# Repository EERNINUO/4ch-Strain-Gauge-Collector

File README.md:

<div align="center">

<!-- Assisted-by: DeepSeek - 文档框架 -->

# 4ch-Strain-Gauge-Collector

创新创业实践课程设计 E4 选题 – 4通道应变信号同步采集模块  
基于 STM32G473，内置 ADC + 高速 SRAM 缓冲 + USB 触发同步

<p align="center">

  <br/>

</p>

</div>

---

## 📌 项目简介

本项目为《创新创业实践课程》课程 E4 选题的硬件与固件设计成果。  
设计基于 **STM32G473**（Arm Cortex-M4F）实现了 **4 通道应变信号同步采集**，支持外部事件触发、高速数据缓存（SRAM）及非易失参数存储（QSPI Flash），并通过 USB/串口实现与 PC 的命令交互与多模块同步。

设计周期：2 周（原理图 + PCB + 仿真 + 文档 + CubeMX工程，无实物焊接与固件代码）  
参考原型：NI‑9237 应变/桥输入模块

**核心指标**：
- 4 通道差分输入（±2.5V，共模 1.65V）
- 12 位内置 ADC，支持硬件过采样
- 4 阶有源低通滤波器（100kHz / 200kHz 可选）
- 最多 4 片 IS61WV204816BLL 高速 SRAM（2M×16bit）
- QSPI Flash 存储固件及标定参数
- USB 2.0 FS + 可线与串口（多模块同步触发）

## 🎯 主要特性

| 模块 | 特性 |
|------|------|
| **模拟前端** | 仪表放大器 (INA) + 1/4 衰减网络 + 4 阶 Sallen-Key 滤波器，净增益 1 |
| **ADC** | 内置 5 个独立 12 位 ADC，支持差分输入，事件触发同步采样 |
| **触发机制** | 片上比较器 (CMP) 整形外部触发信号，直接路由到定时器，响应延迟 < 1µs |
| **数据缓存** | FMC 总线扩展 SRAM（1~4 片），支持连续高速采集 |
| **存储** | QSPI Flash 用于程序 XIP 及标定参数掉电保存 |
| **通信** | USB CDC 虚拟串口 / 可线与硬件串口，支持多机同步 |

---

## 🖥️ 硬件架构概览

详细原理框图及模块说明见 [硬件设计文档](docs/硬件设计文档.md)。

## 🛠️ 开发工具与环境

| 用途 | 工具 | 版本 |
|------|------|------|
| 原理图 & PCB |  KiCad | 10.0 |
| 模拟仿真 | LTspice  | 26.0.1 |
| MCU 配置 | STM32CubeMX | 6.13 |
| 代码生成 | Keil MDK | 5.36  |
| 版本管理 | Git + GitHub | - |

## 📁 仓库结构
```text
4ch-Strain-Gauge-Collector/
├── docs/                     # 设计文档  
│   ├── pic/                  # 文档中用到的图片  
│   ├── hardware_design.md    # 硬件设计文档（原理图、PCB、BOM）  
│   └──  LICENSE              # CC BY-SA 4.0   
├── simulation/               # LTspice 仿真文件  
├── firmware/                 # CubeMX工程与生成代码（CubeMX + Keil）  
│   └── STM32G473.ioc         # CubeMX 配置文件  
├── hardware/                 # 硬件设计源文件  
|   ├── E4                    # Kicad 原理图与 PCB 文件  
│   └── LICENSE # CERN-OHL-S-2.0     
├── README.md                 # 项目说明  
└── LICENSE                   # GPL-3.0
```

## 📜 许可证
Copyright © 2026 EERNINUO

本项目采用**多许可证策略**，不同部分适用不同许可证：

| 组成部分 | 许可证 |
|----------|--------|
| 固件 (MCU/FPGA 代码) | [GNU General Public License v3.0](LICENSE) |
| 硬件设计文件 (原理图、PCB、BOM) | [CERN Open Hardware Licence Version 2 - Strongly Reciprocal](hardware/LICENSE) |
| 文档、图片、README | [Creative Commons Attribution-ShareAlike 4.0 International](docs/LICENSE) |

这意味着：
- 你可以自由使用、修改、分享固件代码，但任何衍生代码也必须以 GPL-3.0 开源。
- 你可以基于硬件设计文件制作、分发物理设备，但必须同时开源你对设计文件的修改，并保留署名。
- 你可以复制和修改文档，但必须同样以 CC BY-SA 4.0 分享，并注明原作者。

## 📧 联系方式

如有问题或建议，请在 GitHub Issues 中提出。

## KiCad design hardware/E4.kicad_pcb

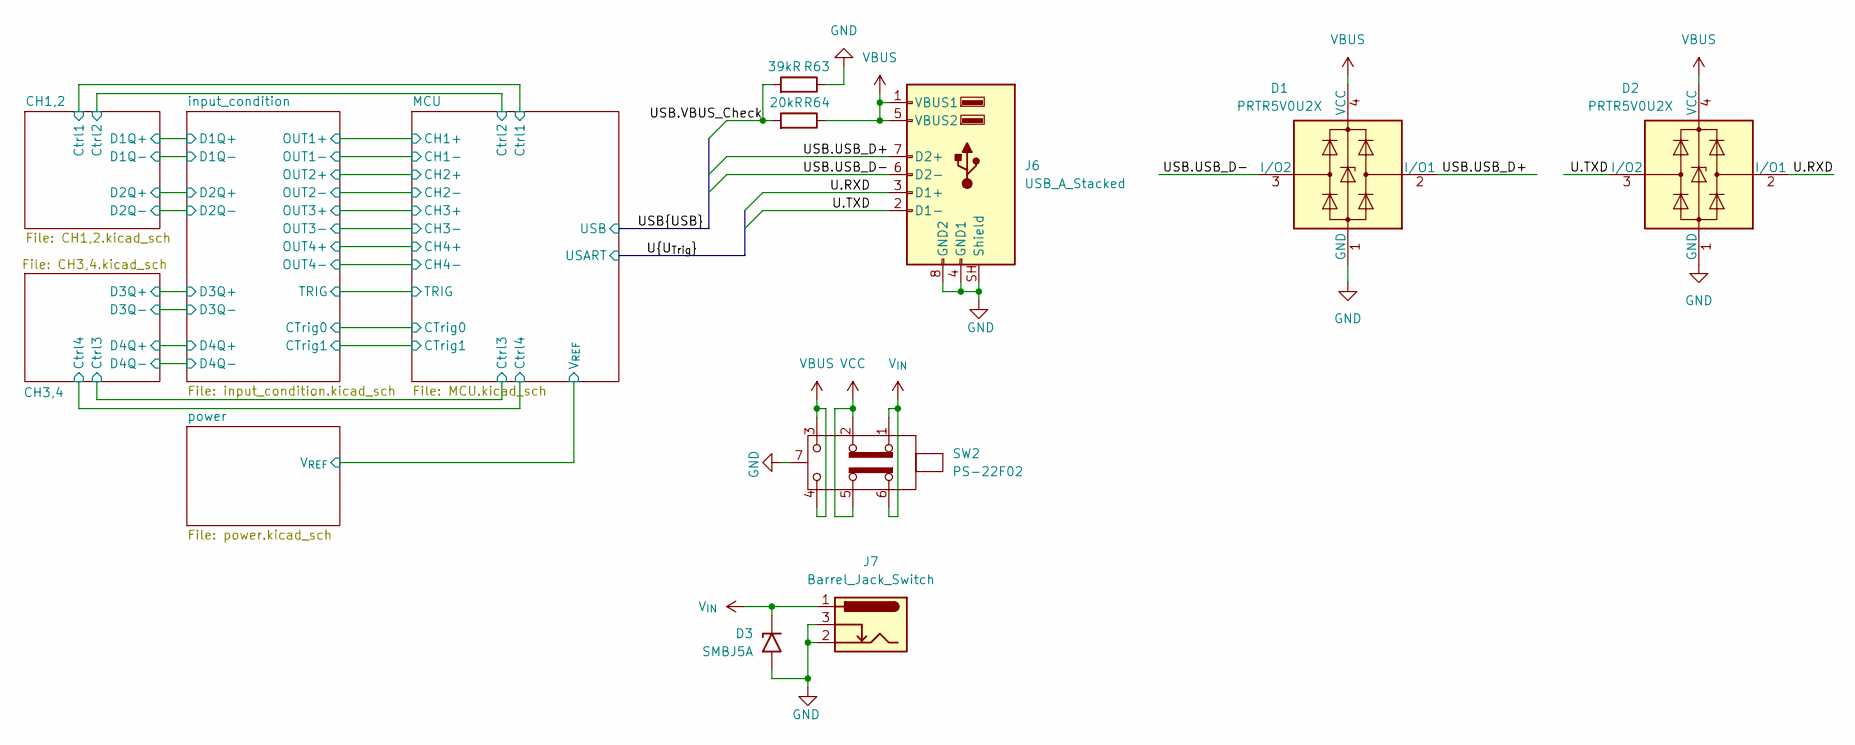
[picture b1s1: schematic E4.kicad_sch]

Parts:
D1, D2: PRTR5V0U2X; SOT-143
D3: SMBJ5A; D_SMF
J6: USB_A_Stacked; USB_A_CUI_UJ2-ADH-TH_Horizontal_Stacked
J7: Barrel_Jack_Switch; BarrelJack_Kycon_KLDX-0202-xC_Horizontal
R63: 39kR; R_0603_1608Metric
R64: 20kR; R_0603_1608Metric
SW2: PS-22F02; SW-TH_G-SWITCH-PS-22F03N

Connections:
/U.RXD: D2.2 (I/O1), J6.3 (D1+); also elsewhere on the board
/U.TXD: D2.3 (I/O2), J6.2 (D1-); also elsewhere on the board
/USB.USB_Check: R63.2, R64.2; also elsewhere on the board
/USB.USB_D+: D1.2 (I/O1), J6.7 (D2+); also elsewhere on the board
/USB.USB_D-: D1.3 (I/O2), J6.6 (D2-); also elsewhere on the board
GND: D1.1 (GND), D2.1 (GND), D3.2 (A2), J6.4 (GND1), J6.8 (GND2), J6.SH (Shield), J7.2, J7.3, R63.1, SW2.7, SW2.8; also elsewhere on the board
VBUS: D1.4 (VCC), D2.4 (VCC), J6.1 (VBUS1), J6.5 (VBUS2), R64.1, SW2.3 (C), SW2.4 (A)
VCC: SW2.2 (B), SW2.5 (B); also elsewhere on the board
V_{IN}: D3.1 (A1), J7.1, SW2.1 (A), SW2.6 (C)

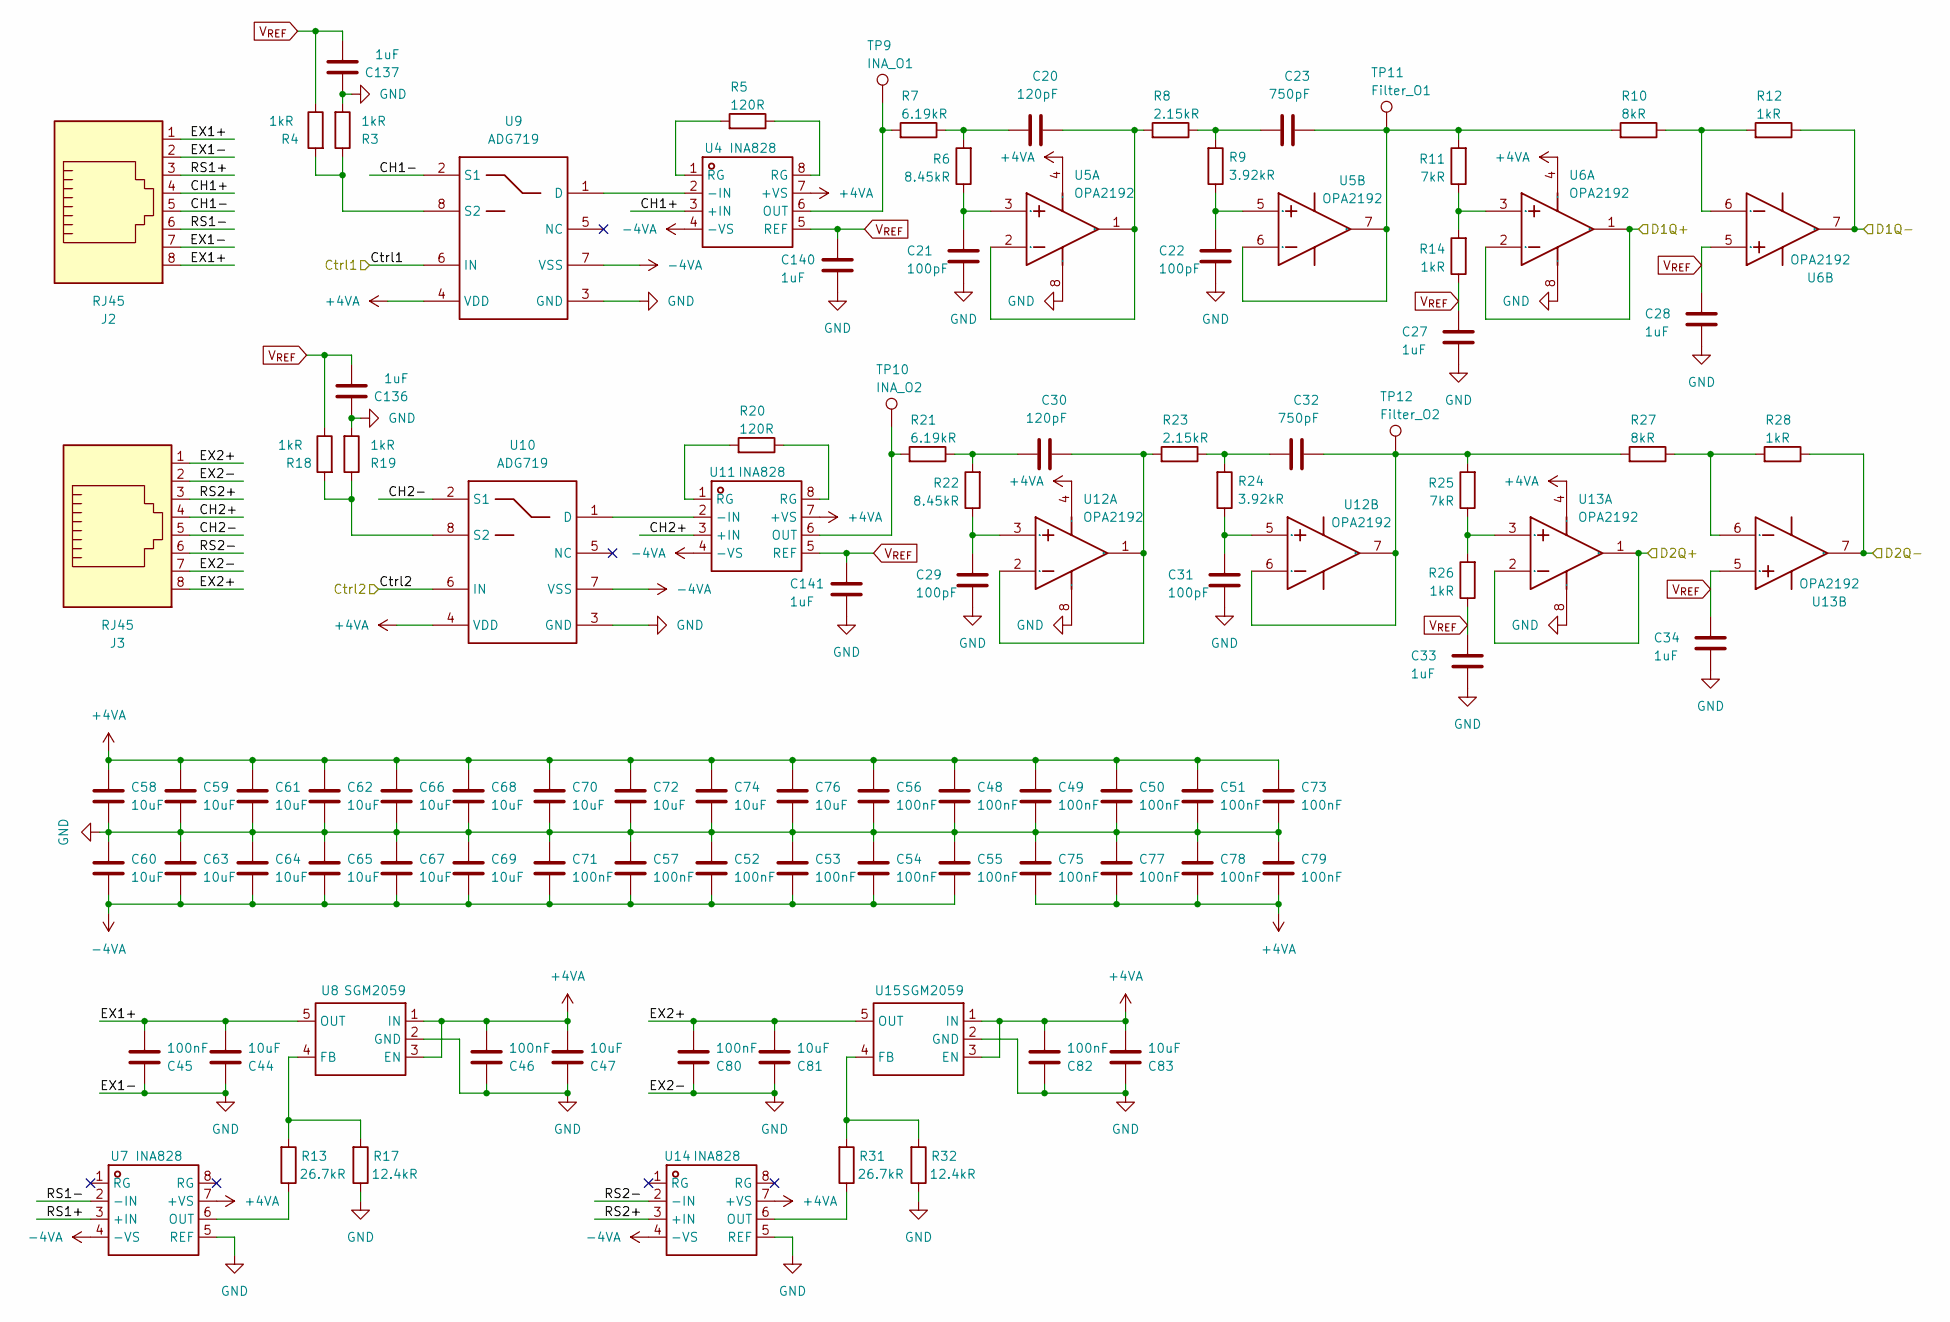
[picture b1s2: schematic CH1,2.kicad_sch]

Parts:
C20, C30: 120pF; C_0603_1608Metric
C21, C22, C29, C31: 100pF; C_0603_1608Metric
C23, C32: 750pF; C_0603_1608Metric
C27, C28, C33, C34, C136, C137, C140, C141: 1uF; C_0603_1608Metric
C44, C47, C58, C59, C60, C61, C62, C63, C64, C65, C66, C67, C68, C69, C70, C72, C74, C76, C81, C83: 10uF; C_0603_1608Metric
C45, C46, C48, C49, C50, C51, C52, C53, C54, C55, C56, C57, C71, C73, C75, C77, C78, C79, C80, C82: 100nF; C_0603_1608Metric
J2, J3: RJ45; RJ45_Amphenol_54602-x08_Horizontal
R3, R4, R12, R14, R18, R19, R26, R28: 1kR; R_0603_1608Metric
R5, R20: 120R; R_0603_1608Metric
R6, R22: 8.45kR; R_0603_1608Metric
R7, R21: 6.19kR; R_0603_1608Metric
R8, R23: 2.15kR; R_0603_1608Metric
R9, R24: 3.92kR; R_0603_1608Metric
R10, R27: 8kR; R_0603_1608Metric
R11, R25: 7kR; R_0603_1608Metric
R13, R31: 26.7kR; R_0603_1608Metric
R17, R32: 12.4kR; R_0603_1608Metric
TP9: INA_O1; TestPoint_Pad_D1.0mm
TP10: INA_O2; TestPoint_Pad_D1.0mm
TP11: Filter_O1; TestPoint_Pad_D1.0mm
TP12: Filter_O2; TestPoint_Pad_D1.0mm
U4, U7, U11, U14: INA828; SOIC-8_3.9x4.9mm_P1.27mm; Manufacturer Part INA828IDR; LCSC Part Name INA828IDR
U5, U6, U12, U13: OPA2192; SOIC-8_3.9x4.9mm_P1.27mm; Manufacturer Part OPA2192IDR; LCSC Part Name OPA2192IDR
U8, U15: SGM2059; SOT-23-5; Manufacturer Part SGM2059-ADJXN5G/TR; LCSC Part Name 300mA，低输入电压、超低噪声、高电源抑制比线性稳压器
U9, U10: ADG719; SOT-23-8; Manufacturer Part ADG619BRTZ-REEL7; LCSC Part Name CMOS单刀双掷开关

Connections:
+4VA: C46.2, C47.2, C48.2, C49.2, C50.2, C51.2, C56.2, C58.1, C59.1, C61.1, C62.1, C66.1, C68.1, C70.1, C72.1, C73.2, C74.1, C75.1, C76.1, C77.1, C78.1, C79.1, C82.2, C83.2, U4.7 (+VS), U5.4 (VSS), U6.4 (VSS), U7.7 (+VS), U8.1 (IN), U8.3 (EN), U9.4 (VDD), U10.4 (VDD), U11.7 (+VS), U12.4 (VSS), U13.4 (VSS), U14.7 (+VS), U15.1 (IN), U15.3 (EN); also elsewhere on the board
-4VA: C52.1, C53.1, C54.1, C55.1, C57.1, C60.2, C63.2, C64.2, C65.2, C67.2, C69.2, C71.1, U4.4 (-VS), U7.4 (-VS), U9.7 (VSS), U10.7 (VSS), U11.4 (-VS), U14.4 (-VS); also elsewhere on the board
/CH1,2/CH1+: J2.4, U4.3 (+IN)
/CH1,2/CH1-: J2.5, U9.2 (S1)
/CH1,2/CH2+: J3.4, U11.3 (+IN)
/CH1,2/CH2-: J3.5, U10.2 (S1)
/CH1,2/Ctrl1: U9.6 (IN); also elsewhere on the board
/CH1,2/Ctrl2: U10.6 (IN); also elsewhere on the board
/CH1,2/D1Q+: U6.1 (VOUTA), U6.2 (VINA-); also elsewhere on the board
/CH1,2/D1Q-: R12.1, U6.7 (VOUTB); also elsewhere on the board
/CH1,2/D2Q+: U13.1 (VOUTA), U13.2 (VINA-); also elsewhere on the board
/CH1,2/D2Q-: R28.1, U13.7 (VOUTB); also elsewhere on the board
/CH1,2/EX1+: C44.2, C45.2, J2.1, J2.8, U8.5 (OUT)
/CH1,2/EX2+: C80.2, C81.2, J3.1, J3.8, U15.5 (OUT)
/CH1,2/RS1+: J2.3, U7.3 (+IN)
/CH1,2/RS1-: J2.6, U7.2 (-IN)
/CH1,2/RS2+: J3.3, U14.3 (+IN)
/CH1,2/RS2-: J3.6, U14.2 (-IN)
GND: C21.2, C22.2, C27.2, C28.2, C29.2, C31.2, C33.2, C34.2, C44.1, C45.1, C46.1, C47.1, C48.1, C49.1, C50.1, C51.1, C52.2, C53.2, C54.2, C55.2, C56.1, C57.2, C58.2, C59.2, C60.1, C61.2, C62.2, C63.1, C64.1, C65.1, C66.2, C67.1, C68.2, C69.1, C70.2, C71.2, C72.2, C73.1, C74.2, C75.2, C76.2, C77.2, C78.2, C79.2, C80.1, C81.1, C82.1, C83.1, C136.1, C137.1, C140.2, C141.2, J2.2, J2.7, J3.2, J3.7, R3.2, R17.1, R19.2, R32.1, U5.8 (VDD), U6.8 (VDD), U7.5 (REF), U8.2 (GND), U9.3 (GND), U10.3 (GND), U12.8 (VDD), U13.8 (VDD), U14.5 (REF), U15.2 (GND); also elsewhere on the board
unnamed: C20.2, R6.2, R7.1
unnamed: C23.2, R8.1, R9.2
unnamed: C30.2, R21.1, R22.2
unnamed: C32.2, R23.1, R24.2
unnamed: R5.1, U4.8 (RG)
unnamed: R5.2, U4.1 (RG)
unnamed: R20.1, U11.8 (RG)
unnamed: R20.2, U11.1 (RG)
unnamed: U4.2 (-IN), U9.1 (D)
unnamed: R7.2, TP9.1 (1_1), U4.6 (OUT)
unnamed: C21.1, R6.1, U5.3 (VINA+)
unnamed: C20.1, R8.2, U5.1 (VOUTA), U5.2 (VINA-)
unnamed: C22.1, R9.1, U5.5 (VINB+)
unnamed: C23.1, R10.2, R11.2, TP11.1 (1_1), U5.6 (VINB-), U5.7 (VOUTB)
unnamed: R11.1, R14.2, U6.3 (VINA+)
unnamed: R10.1, R12.2, U6.6 (VINB-)
unnamed: R13.1, U7.6 (OUT)
unnamed: R13.2, R17.2, U8.4 (FB)
unnamed: R3.1, R4.2, U9.8 (S2)
unnamed: U10.1 (D), U11.2 (-IN)
unnamed: R18.2, R19.1, U10.8 (S2)
unnamed: R21.2, TP10.1 (1_1), U11.6 (OUT)
unnamed: C29.1, R22.1, U12.3 (VINA+)
unnamed: C30.1, R23.2, U12.1 (VOUTA), U12.2 (VINA-)
unnamed: C31.1, R24.1, U12.5 (VINB+)
unnamed: C32.1, R25.2, R27.2, TP12.1 (1_1), U12.6 (VINB-), U12.7 (VOUTB)
unnamed: R25.1, R26.2, U13.3 (VINA+)
unnamed: R27.1, R28.2, U13.6 (VINB-)
unnamed: R31.1, U14.6 (OUT)
unnamed: R31.2, R32.2, U15.4 (FB)

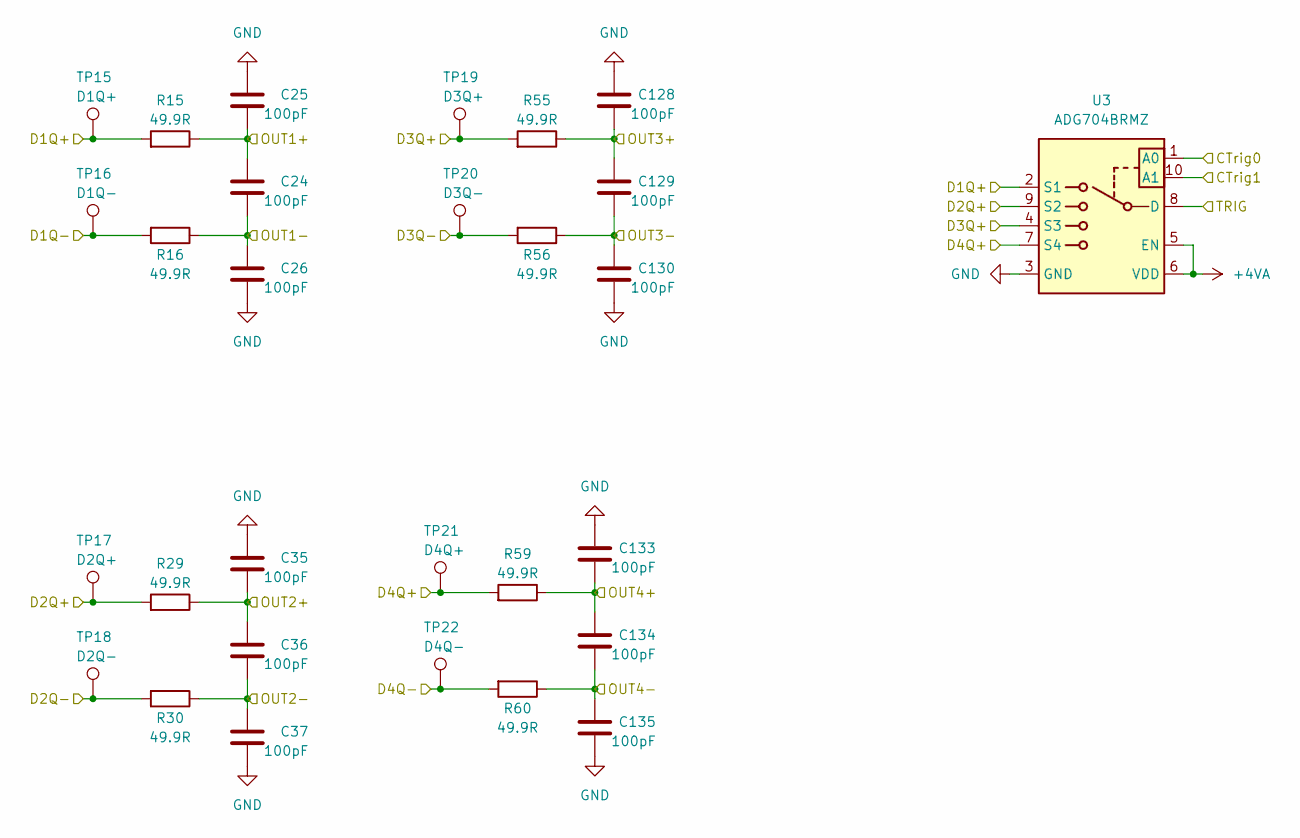
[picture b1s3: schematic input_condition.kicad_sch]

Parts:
C24, C25, C26, C35, C36, C37, C128, C129, C130, C133, C134, C135: 100pF; C_0402_1005Metric
R15, R16, R29, R30, R55, R56, R59, R60: 49.9R; R_0402_1005Metric
TP15: D1Q+; TestPoint_Pad_D1.0mm
TP16: D1Q-; TestPoint_Pad_D1.0mm
TP17: D2Q+; TestPoint_Pad_D1.0mm
TP18: D2Q-; TestPoint_Pad_D1.0mm
TP19: D3Q+; TestPoint_Pad_D1.0mm
TP20: D3Q-; TestPoint_Pad_D1.0mm
TP21: D4Q+; TestPoint_Pad_D1.0mm
TP22: D4Q-; TestPoint_Pad_D1.0mm
U3: ADG704BRMZ; TSSOP-10_3x3mm_P0.5mm

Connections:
+4VA: U3.5 (EN), U3.6 (VDD); also elsewhere on the board
/CH1,2/D1Q+: R15.2, TP15.1 (1_1), U3.2 (S1); also elsewhere on the board
/CH1,2/D1Q-: R16.2, TP16.1 (1_1); also elsewhere on the board
/CH1,2/D2Q+: R29.2, TP17.1 (1_1), U3.9 (S2); also elsewhere on the board
/CH1,2/D2Q-: R30.2, TP18.1 (1_1); also elsewhere on the board
/CH3,4/D3Q+: R55.2, TP19.1 (1_1), U3.4 (S3); also elsewhere on the board
/CH3,4/D3Q-: R56.2, TP20.1 (1_1); also elsewhere on the board
/CH3,4/D4Q+: R59.2, TP21.1 (1_1), U3.7 (S4); also elsewhere on the board
/CH3,4/D4Q-: R60.2, TP22.1 (1_1); also elsewhere on the board
/MCU/CH1+: C24.1, C25.2, R15.1; also elsewhere on the board
/MCU/CH1-: C24.2, C26.1, R16.1; also elsewhere on the board
/MCU/CH2+: C35.2, C36.1, R29.1; also elsewhere on the board
/MCU/CH2-: C36.2, C37.1, R30.1; also elsewhere on the board
/MCU/CH3+: C128.2, C129.1, R55.1; also elsewhere on the board
/MCU/CH3-: C129.2, C130.1, R56.1; also elsewhere on the board
/MCU/CH4+: C133.2, C134.1, R59.1; also elsewhere on the board
/MCU/CH4-: C134.2, C135.1, R60.1; also elsewhere on the board
/MCU/CTrig0: U3.1 (A0); also elsewhere on the board
/MCU/CTrig1: U3.10 (A1); also elsewhere on the board
/MCU/TRIG: U3.8 (D); also elsewhere on the board
GND: C25.1, C26.2, C35.1, C37.2, C128.1, C130.2, C133.1, C135.2, U3.3 (GND); also elsewhere on the board

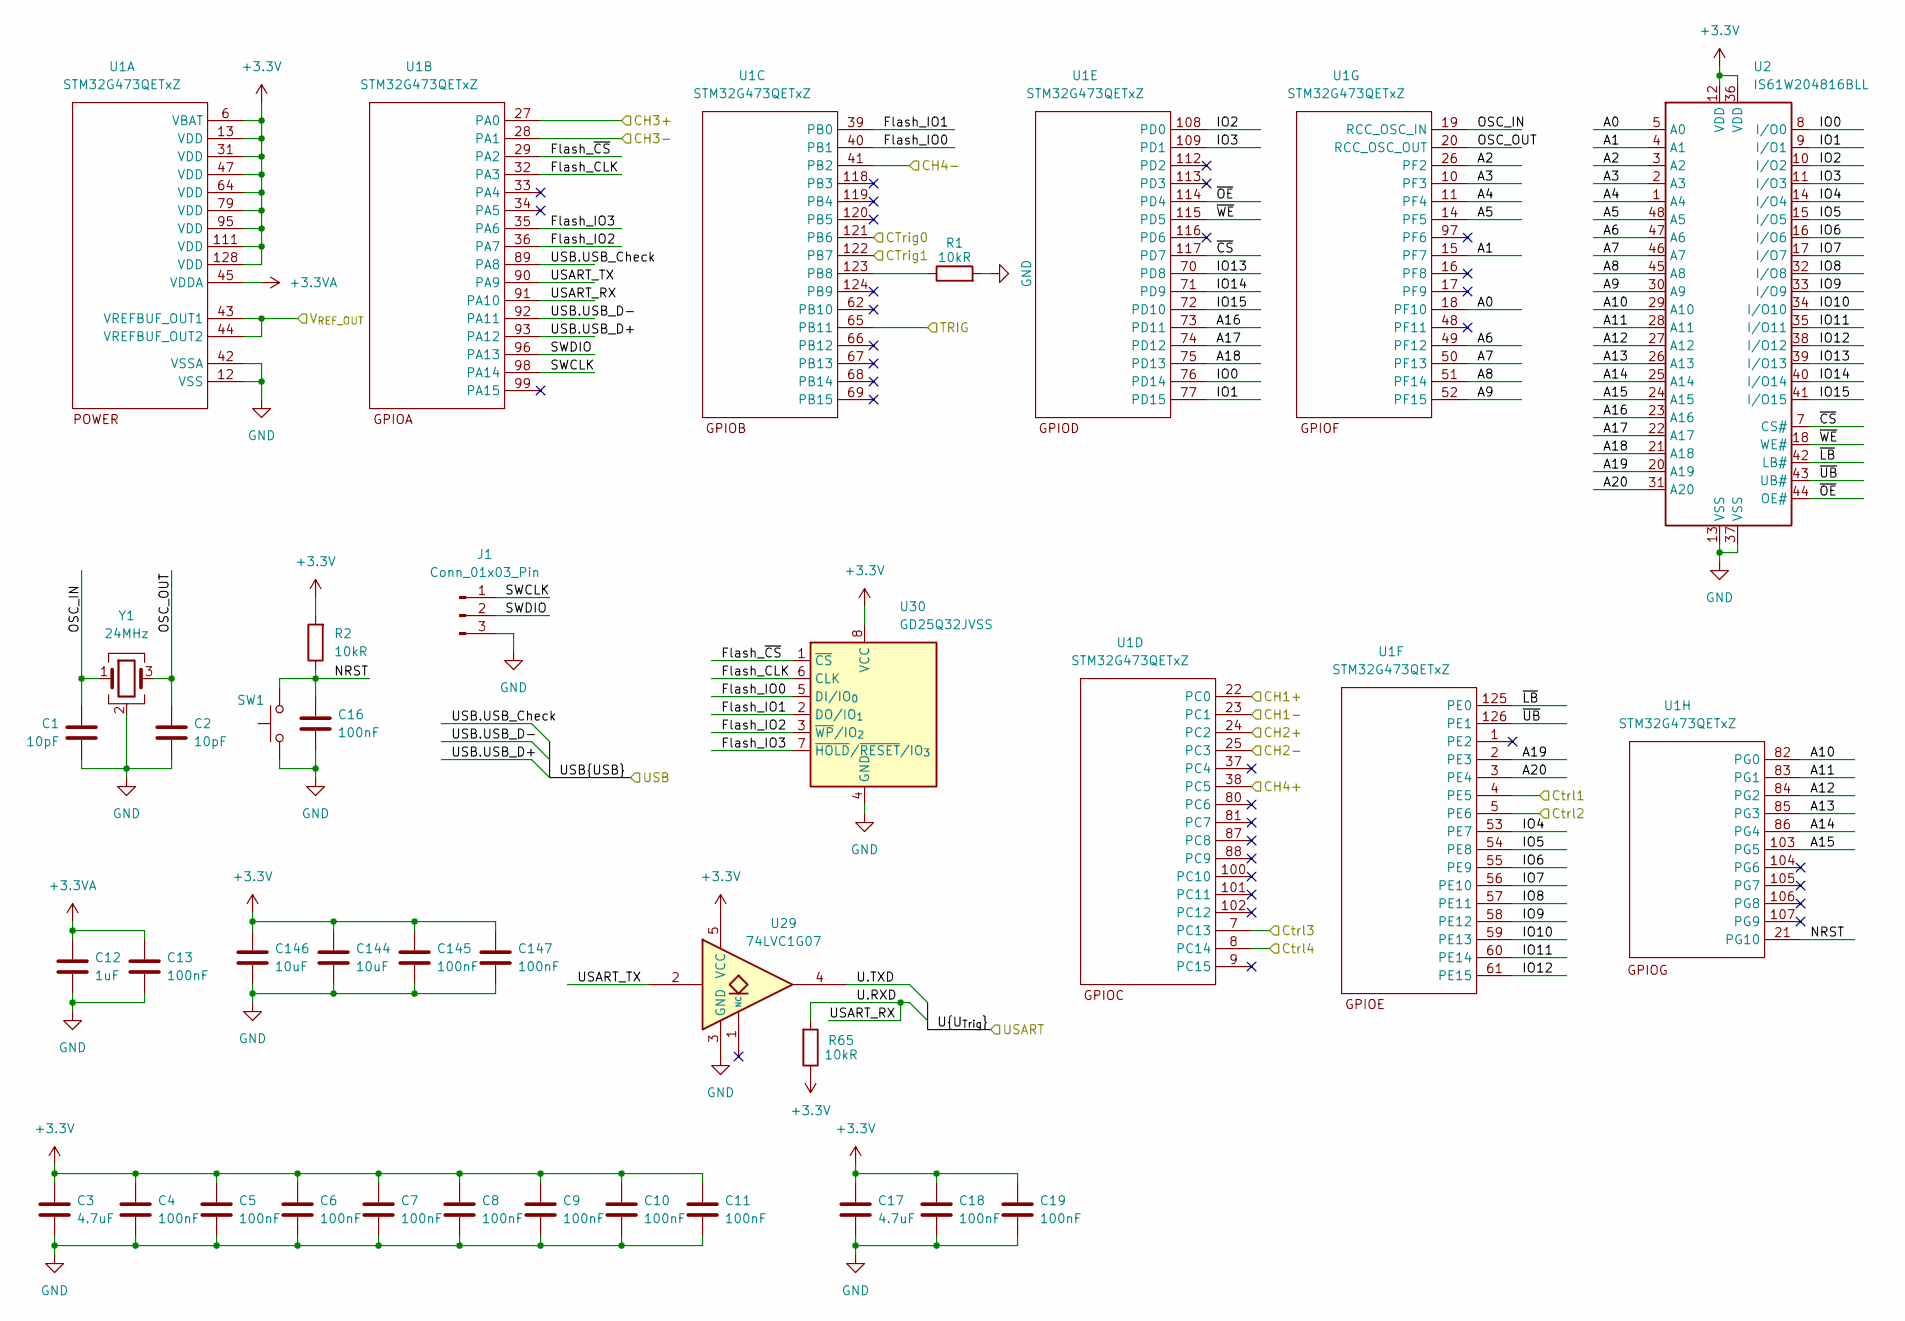
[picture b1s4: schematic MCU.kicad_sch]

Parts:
C1, C2: 10pF; C_0402_1005Metric
C3, C17: 4.7uF; C_0603_1608Metric
C4, C13: 100nF; C_0402_1005Metric
C5, C6, C7, C8, C9, C10, C11, C16, C18, C19, C145, C147: 100nF; C_0603_1608Metric
C12: 1uF; C_0402_1005Metric
C144, C146: 10uF; C_0603_1608Metric
J1: Conn_01x03_Pin; PinHeader_1x03_P1.00mm_Vertical
R1, R2, R65: 10kR; R_0603_1608Metric
SW1: SW_MEC_5G; SW_SPST_FSMSM
U1: STM32G473QETxZ; LQFP-128_14x14mm_P0.4mm
U2: IS61W204816BLL; TSOP-I-48_18.4x12mm_P0.5mm; Manufacturer Part IS61WV204816BLL-10TLI; LCSC Part Name IS61WV204816BLL 10TLI
U29: 74LVC1G07; SOT-23-5
U30: GD25Q32JVSS; SOIC-8_5.3x5.3mm_P1.27mm
Y1: 24MHz; Crystal_SMD_2016-4Pin_2.0x1.6mm

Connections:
+3.3V: C3.1, C4.1, C5.1, C6.1, C7.1, C8.1, C9.1, C10.1, C11.1, C17.1, C18.1, C19.1, C144.1, C145.1, C146.1, C147.1, R2.2, R65.1, U1.6 (VBAT), U1.13 (VDD), U1.31 (VDD), U1.47 (VDD), U1.64 (VDD), U1.79 (VDD), U1.95 (VDD), U1.111 (VDD), U1.128 (VDD), U2.12 (VDD), U2.36 (VDD), U29.5 (VCC), U30.8 (VCC); also elsewhere on the board
+3.3VA: C12.1, C13.1, U1.45 (VDDA); also elsewhere on the board
/CH1,2/Ctrl1: U1.4 (PE5); also elsewhere on the board
/CH1,2/Ctrl2: U1.5 (PE6); also elsewhere on the board
/CH3,4/Ctrl3: U1.7 (PC13); also elsewhere on the board
/CH3,4/Ctrl4: U1.8 (PC14); also elsewhere on the board
/MCU/A0: U1.18 (PF10), U2.5 (A0)
/MCU/A1: U1.15 (PF7), U2.4 (A1)
/MCU/A2: U1.26 (PF2), U2.3 (A2)
/MCU/A3: U1.10 (PF3), U2.2 (A3)
/MCU/A4: U1.11 (PF4), U2.1 (A4)
/MCU/A5: U1.14 (PF5), U2.48 (A5)
/MCU/A6: U1.49 (PF12), U2.47 (A6)
/MCU/A7: U1.50 (PF13), U2.46 (A7)
/MCU/A8: U1.51 (PF14), U2.45 (A8)
/MCU/A9: U1.52 (PF15), U2.30 (A9)
/MCU/A10: U1.82 (PG0), U2.29 (A10)
/MCU/A11: U1.83 (PG1), U2.28 (A11)
/MCU/A12: U1.84 (PG2), U2.27 (A12)
/MCU/A13: U1.85 (PG3), U2.26 (A13)
/MCU/A14: U1.86 (PG4), U2.25 (A14)
/MCU/A15: U1.103 (PG5), U2.24 (A15)
/MCU/A16: U1.73 (PD11), U2.23 (A16)
/MCU/A17: U1.74 (PD12), U2.22 (A17)
/MCU/A18: U1.75 (PD13), U2.21 (A18)
/MCU/A19: U1.2 (PE3), U2.20 (A19)
/MCU/A20: U1.3 (PE4), U2.31 (A20)
/MCU/CH1+: U1.22 (PC0); also elsewhere on the board
/MCU/CH1-: U1.23 (PC1); also elsewhere on the board
/MCU/CH2+: U1.24 (PC2); also elsewhere on the board
/MCU/CH2-: U1.25 (PC3); also elsewhere on the board
/MCU/CH3+: U1.27 (PA0); also elsewhere on the board
/MCU/CH3-: U1.28 (PA1); also elsewhere on the board
/MCU/CH4+: U1.38 (PC5); also elsewhere on the board
/MCU/CH4-: U1.41 (PB2); also elsewhere on the board
/MCU/CTrig0: U1.121 (PB6); also elsewhere on the board
/MCU/CTrig1: U1.122 (PB7); also elsewhere on the board
/MCU/Flash_CLK: U1.32 (PA3), U30.6 (CLK)
/MCU/Flash_IO0: U1.40 (PB1), U30.5 (DI/IO_{0})
/MCU/Flash_IO1: U1.39 (PB0), U30.2 (DO/IO_{1})
/MCU/Flash_IO2: U1.36 (PA7), U30.3 (~WP/IO_{2})
/MCU/Flash_IO3: U1.35 (PA6), U30.7 (~HOLD/~RESET/IO_{3})
/MCU/Flash_~CS: U1.29 (PA2), U30.1 (~CS)
/MCU/IO0: U1.76 (PD14), U2.8 (I/O0)
/MCU/IO1: U1.77 (PD15), U2.9 (I/O1)
/MCU/IO2: U1.108 (PD0), U2.10 (I/O2)
/MCU/IO3: U1.109 (PD1), U2.11 (I/O3)
/MCU/IO4: U1.53 (PE7), U2.14 (I/O4)
/MCU/IO5: U1.54 (PE8), U2.15 (I/O5)
/MCU/IO6: U1.55 (PE9), U2.16 (I/O6)
/MCU/IO7: U1.56 (PE10), U2.17 (I/O7)
/MCU/IO8: U1.57 (PE11), U2.32 (I/O8)
/MCU/IO9: U1.58 (PE12), U2.33 (I/O9)
/MCU/IO10: U1.59 (PE13), U2.34 (I/O10)
/MCU/IO11: U1.60 (PE14), U2.35 (I/O11)
/MCU/IO12: U1.61 (PE15), U2.38 (I/O12)
/MCU/IO13: U1.70 (PD8), U2.39 (I/O13)
/MCU/IO14: U1.71 (PD9), U2.40 (I/O14)
/MCU/IO15: U1.72 (PD10), U2.41 (I/O15)
/MCU/NRST: C16.1, R2.1, SW1.2 (B), U1.21 (PG10)
/MCU/OSC_IN: C1.1, U1.19 (RCC_OSC_IN), Y1.1
/MCU/OSC_OUT: C2.1, U1.20 (RCC_OSC_OUT), Y1.3
/MCU/SWCLK: J1.1, U1.98 (PA14)
/MCU/SWDIO: J1.2, U1.96 (PA13)
/MCU/TRIG: U1.65 (PB11); also elsewhere on the board
/MCU/USART_TX: U1.90 (PA9), U29.2
/MCU/V_{REF_OUT}: U1.43 (VREFBUF_OUT1), U1.44 (VREFBUF_OUT2); also elsewhere on the board
/MCU/~CS: U1.117 (PD7), U2.7 (CS#)
/MCU/~LB: U1.125 (PE0), U2.42 (LB#)
/MCU/~OE: U1.114 (PD4), U2.44 (OE#)
/MCU/~UB: U1.126 (PE1), U2.43 (UB#)
/MCU/~WE: U1.115 (PD5), U2.18 (WE#)
/U.RXD: R65.2, U1.91 (PA10); also elsewhere on the board
/U.TXD: U29.4; also elsewhere on the board
/USB.USB_Check: U1.89 (PA8); also elsewhere on the board
/USB.USB_D+: U1.93 (PA12); also elsewhere on the board
/USB.USB_D-: U1.92 (PA11); also elsewhere on the board
GND: C1.2, C2.2, C3.2, C4.2, C5.2, C6.2, C7.2, C8.2, C9.2, C10.2, C11.2, C12.2, C13.2, C16.2, C17.2, C18.2, C19.2, C144.2, C145.2, C146.2, C147.2, J1.3, R1.2, SW1.1 (A), U1.12 (VSS), U1.30 (VSS), U1.42 (VSSA), U1.46 (VSS), U1.63 (VSS), U1.78 (VSS), U1.94 (VSS), U1.110 (VSS), U1.127 (VSS), U2.13 (VSS), U2.37 (VSS), U29.3 (GND), U30.4 (GND), Y1.2 (G), Y1.4 (G); also elsewhere on the board
unnamed: R1.1, U1.123 (PB8)

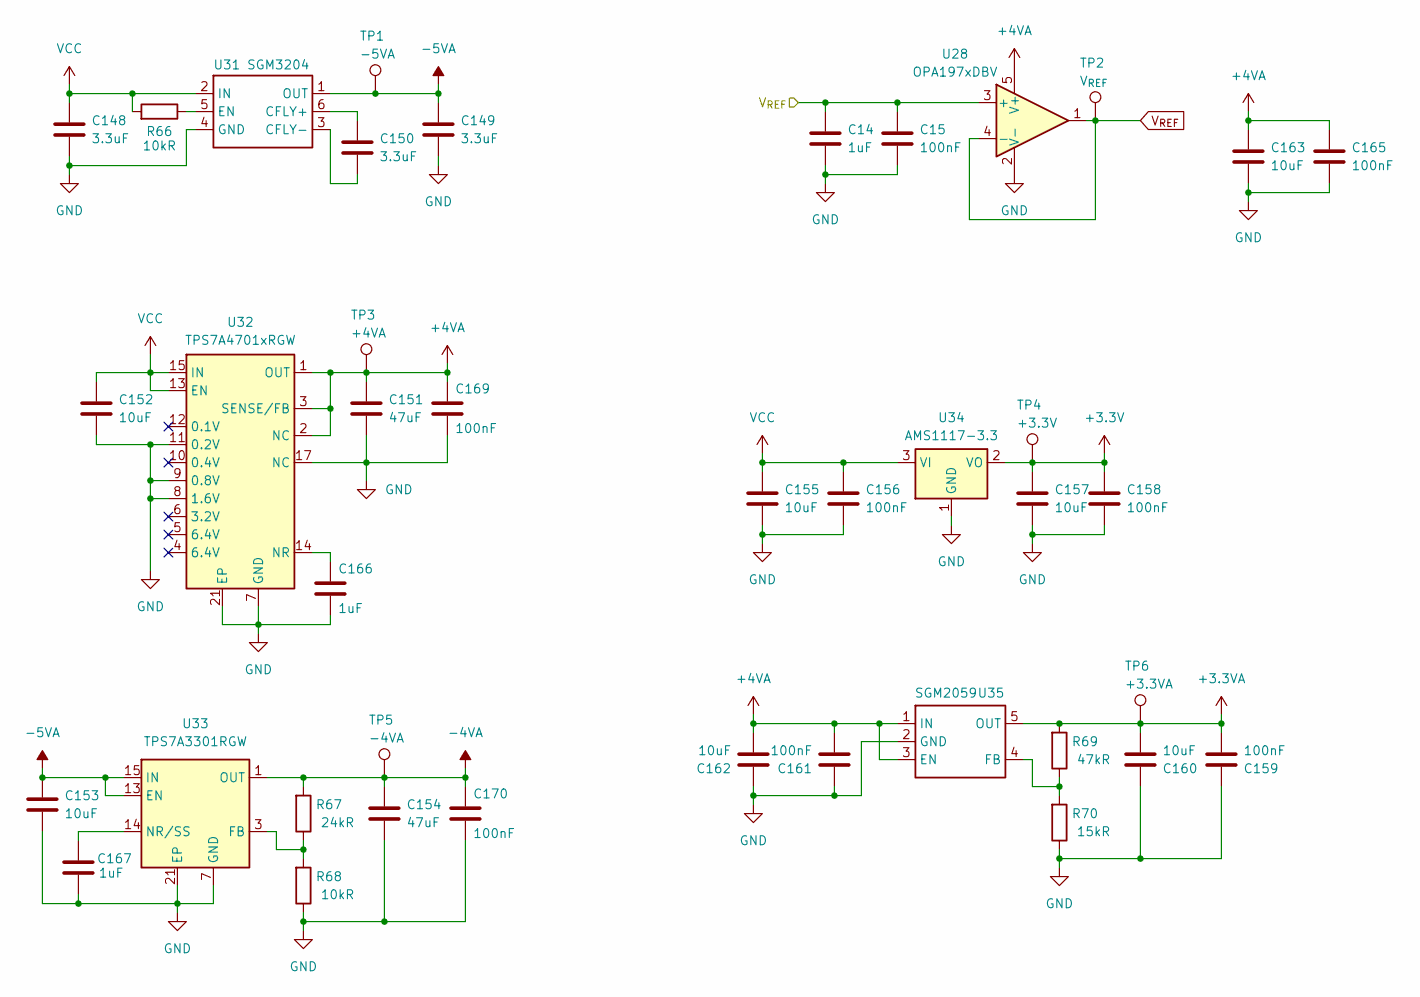
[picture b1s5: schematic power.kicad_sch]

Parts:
C14, C166, C167: 1uF; C_0603_1608Metric
C15, C156, C158, C159, C161, C165, C169, C170: 100nF; C_0603_1608Metric
C148, C149, C150: 3.3uF; C_0603_1608Metric
C151, C154: 47uF; C_1206_3216Metric
C152, C153, C155, C157, C160, C162, C163: 10uF; C_0603_1608Metric
R66, R68: 10kR; R_0603_1608Metric
R67: 24kR; R_0603_1608Metric
R69: 47kR; R_0603_1608Metric
R70: 15kR; R_0603_1608Metric
TP1: -5VA; TestPoint_Pad_D1.0mm
TP2: V_{REF}; TestPoint_Pad_D1.0mm
TP3: +4VA; TestPoint_Pad_D1.0mm
TP4: +3.3V; TestPoint_Pad_D1.0mm
TP5: -4VA; TestPoint_Pad_D1.0mm
TP6: +3.3VA; TestPoint_Pad_D1.0mm
U28: OPA197xDBV; SOT-23-5
U31: SGM3204; SOT-23-6; Manufacturer Part SGM3204YN6G/TR; LCSC Part Name SGM3204YN6G/TR
U32: TPS7A4701xRGW; Texas_RGW0020A_VQFN-20-1EP_5x5mm_P0.65mm_EP3.15x3.15mm_Ther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
U33: TPS7A3301RGW; Texas_RGW0020A_VQFN-20-1EP_5x5mm_P0.65mm_EP3.15x3.15mm_Ther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
U34: AMS1117-3.3; SOT-223-3_TabPin2
U35: SGM2059; SOT-23-5; Manufacturer Part SGM2059-ADJXN5G/TR; LCSC Part Name 300mA，低输入电压、超低噪声、高电源抑制比线性稳压器

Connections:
+3.3V: C157.1, C158.1, TP4.1 (1_1), U34.2 (VO); also elsewhere on the board
+3.3VA: C159.2, C160.2, R69.2, TP6.1 (1_1), U35.5 (OUT); also elsewhere on the board
+4VA: C151.1, C161.2, C162.2, C163.1, C165.2, C169.2, TP3.1 (1_1), U28.5 (V+), U32.1 (OUT), U32.2 (NC), U32.3 (SENSE/FB), U32.20 (OUT), U35.1 (IN), U35.3 (EN); also elsewhere on the board
-4VA: C154.1, C170.2, R67.2, TP5.1 (1_1), U33.1 (OUT), U33.20 (OUT); also elsewhere on the board
-5VA: C149.1, C153.1, TP1.1 (1_1), U31.1 (OUT), U33.13 (EN), U33.15 (IN), U33.16 (IN)
/MCU/V_{REF_OUT}: C14.1, C15.1, U28.3 (+); also elsewhere on the board
GND: C14.2, C15.2, C148.2, C149.2, C151.2, C152.2, C153.2, C154.2, C155.2, C156.2, C157.2, C158.2, C159.1, C160.1, C161.1, C162.1, C163.2, C165.1, C166.1, C167.1, C169.1, C170.1, R68.1, R70.1, U28.2 (V-), U31.4 (GND), U32.7 (GND), U32.8 (1.6V), U32.9 (0.8V), U32.11 (0.2V), U32.17 (NC), U32.18 (NC), U32.19 (NC), U32.21 (EP), U33.7 (GND), U33.21 (EP), U34.1 (GND), U35.2 (GND); also elsewhere on the board
unnamed: C150.1, U31.6 (CFLY+)
unnamed: C150.2, U31.3 (CFLY-)
unnamed: R66.1, U31.5 (EN)
unnamed: C166.2, U32.14 (NR)
unnamed: R67.1, R68.2, U33.3 (FB)
unnamed: C167.2, U33.14 (NR/SS)
unnamed: R69.1, R70.2, U35.4 (FB)
VCC: C148.1, C152.1, C155.1, C156.1, R66.2, U31.2 (IN), U32.13 (EN), U32.15 (IN), U32.16 (IN), U34.3 (VI); also elsewhere on the board
